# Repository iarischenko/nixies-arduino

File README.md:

# nixies-arduino
The repository contains sch, pcb and source code files for clock based on
IN12 nixie tubes.
The clock is based on custom stm32 board, MAX1771 boost converter, HV5812 high
voltage drivers, PEC16 encoder and FUSB302 usb pd phy.

## folder structure
freecad-project: case FreeCAD 3d models\
kicad-projects : pcb's KiCAD projects\
software       : libopencm3 based software for stm32 based MCU board

## IN12 v3
(master)

## IN12 v2
see v2 tag
### IN12 v2 (demo, clickable video)

## IN12 v1
see v1 tag
Prototype photo:

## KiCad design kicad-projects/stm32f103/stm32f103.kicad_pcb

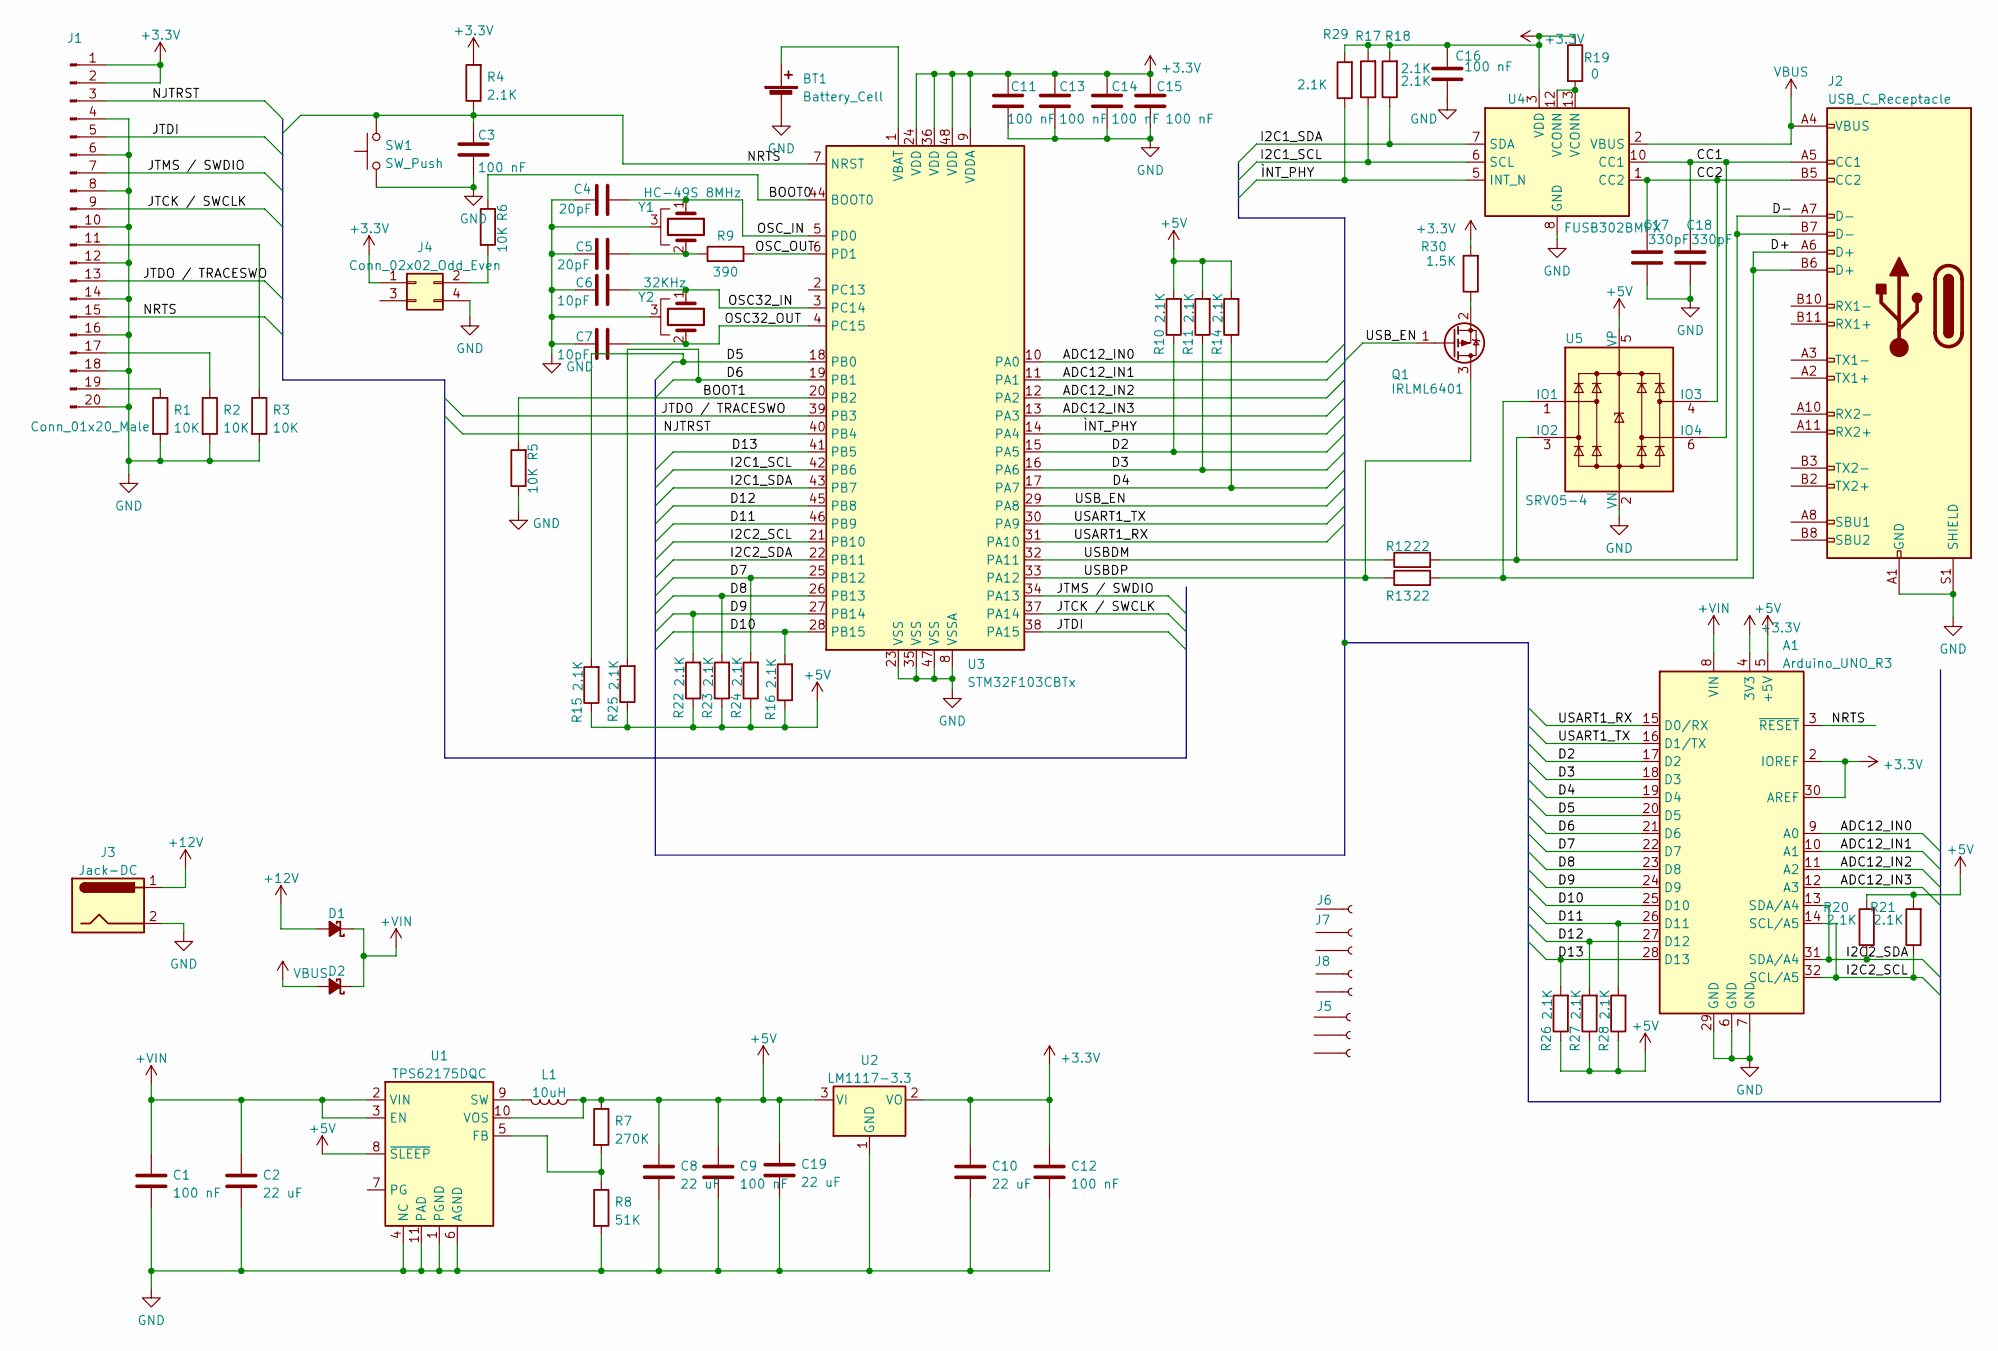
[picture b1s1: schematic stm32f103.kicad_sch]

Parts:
A1: Arduino_UNO_R3; Arduino_UNO_R3_WithMountingHoles_inverted
BT1: Battery_Cell; BatteryHolder_Keystone_1060_1x2032
C1, C3, C9, C11, C12, C13, C14, C15, C16: 100 nF; C_0805_2012Metric_Pad1.18x1.45mm_HandSolder
C2, C8, C10, C19: 22 uF; C_1206_3216Metric_Pad1.33x1.80mm_HandSolder
C4, C5: 20pF; C_0805_2012Metric_Pad1.18x1.45mm_HandSolder
C6, C7: 10pF; C_0805_2012Metric_Pad1.18x1.45mm_HandSolder
C17, C18: 330pF; C_0805_2012Metric_Pad1.18x1.45mm_HandSolder
D1, D2: D_Schottky_Small_Filled; D_SMA
J1: Conn_01x20_Male; PinHeader_2x10_P2.54mm_Vertical
J2: USB_C_Receptacle; USB_C_Receptacle_HRO_TYPE-C-31-M-12
J3: Jack-DC; BarrelJack_Horizontal
J4: Conn_02x02_Odd_Even; PinHeader_2x02_P2.54mm_Vertical
J5: Conn_01x10_Female; PinSocket_1x10_P2.54mm_Vertical
J6: Conn_01x06_Female; PinSocket_1x06_P2.54mm_Vertical
J7, J8: Conn_01x08_Female; PinSocket_1x08_P2.54mm_Vertical
L1: 10uH; L_Vishay_IHLP-4040
Q1: IRLML6401; SOT-23
R1, R2, R3, R5, R6: 10K; R_0805_2012Metric_Pad1.20x1.40mm_HandSolder
R4, R10, R11, R14, R15, R16, R17, R18, R20, R21, R22, R23, R24, R25, R26, R27, R28, R29: 2.1K; R_0805_2012Metric_Pad1.20x1.40mm_HandSolder
R7: 270K; R_0805_2012Metric_Pad1.20x1.40mm_HandSolder
R8: 51K; R_0805_2012Metric_Pad1.20x1.40mm_HandSolder
R9: 390; R_0805_2012Metric_Pad1.20x1.40mm_HandSolder
R12, R13: 22; R_0805_2012Metric_Pad1.20x1.40mm_HandSolder
R19: 0; R_0805_2012Metric_Pad1.20x1.40mm_HandSolder
R30: 1.5K; R_0805_2012Metric_Pad1.20x1.40mm_HandSolder
SW1: SW_Push; SW_Push_1P1T_NO_CK_KSC7xxJ
U1: TPS62175DQC; WSON-10-1EP_2x3mm_P0.5mm_EP0.84x2.4mm_ThermalVias
U2: LM1117-3.3; SOT-223-3_TabPin2
U3: STM32F103CBTx; LQFP-48_7x7mm_P0.5mm
U4: FUSB302BMPX; WQFN-14-1EP_2.5x2.5mm_P0.5mm_EP1.45x1.45mm
U5: SRV05-4; SOT-23-6
Y1: HC-49S 8MHz; Crystal_SMD_HC49-SD
Y2: 32KHz; Crystal_C38-LF_D3.0mm_L8.0mm_Horizontal_1EP_style2

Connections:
+3.3V: A1.2 (IOREF), A1.4 (3V3), A1.30 (AREF), C10.1, C11.1, C12.1, C13.1, C14.1, C15.1, C16.1, J1.1, J1.2, J4.1, R4.2, R17.2, R18.2, R19.1, R29.2, R30.2, U2.2 (VO), U3.9 (VDDA), U3.24 (VDD), U3.36 (VDD), U3.48 (VDD), U4.3 (VDD), U4.4 (VDD)
+5V: A1.5 (+5V), C8.1, C9.1, C19.1, L1.1, R7.1, R10.2, R11.2, R14.2, R15.1, R16.1, R20.2, R21.2, R22.1, R23.1, R24.1, R25.1, R26.1, R27.1, R28.1, U1.8 (~SLEEP), U1.10 (VOS), U2.3 (VI), U5.5 (VP)
+12V: D1.2 (A), J3.1
+VIN: A1.8 (VIN), C1.1, C2.1, D1.1 (K), D2.1 (K), U1.2 (VIN), U1.3 (EN)
/ADC12_IN0: A1.9 (A0), U3.10 (PA0)
/ADC12_IN1: A1.10 (A1), U3.11 (PA1)
/ADC12_IN2: A1.11 (A2), U3.12 (PA2)
/ADC12_IN3: A1.12 (A3), U3.13 (PA3)
/BOOT0: R6.1, U3.44 (BOOT0)
/BOOT1: R5.2, U3.20 (PB2)
/CC1: C18.2, J2.A5 (CC1), U4.10 (CC1), U4.11 (CC1), U5.6 (IO4)
/CC2: C17.2, J2.B5 (CC2), U4.1 (CC2), U4.14 (CC2), U5.4 (IO3)
/D2: A1.17 (D2), R10.1, U3.15 (PA5)
/D3: A1.18 (D3), R11.1, U3.16 (PA6)
/D4: A1.19 (D4), R14.1, U3.17 (PA7)
/D5: A1.20 (D5), R15.2, U3.18 (PB0)
/D6: A1.21 (D6), R25.2, U3.19 (PB1)
/D7: A1.22 (D7), R24.2, U3.25 (PB12)
/D8: A1.23 (D8), R23.2, U3.26 (PB13)
/D9: A1.24 (D9), R22.2, U3.27 (PB14)
/D10: A1.25 (D10), R16.2, U3.28 (PB15)
/D11: A1.26 (D11), R28.2, U3.46 (PB9)
/D12: A1.27 (D12), R27.2, U3.45 (PB8)
/D13: A1.28 (D13), R26.2, U3.41 (PB5)
/D+: J2.A6 (D+), J2.B6 (D+), R13.2, U5.1 (IO1)
/D-: J2.A7 (D-), J2.B7 (D-), R12.2, U5.3 (IO2)
/I2C1_SCL: R17.1, U3.42 (PB6), U4.6 (SCL)
/I2C1_SDA: R18.1, U3.43 (PB7), U4.7 (SDA)
/I2C2_SCL: A1.14 (SCL/A5), A1.32 (SCL/A5), R21.1, U3.21 (PB10)
/I2C2_SDA: A1.13 (SDA/A4), A1.31 (SDA/A4), R20.1, U3.22 (PB11)
/JTCK / SWCLK: J1.9, U3.37 (PA14)
/JTDI: J1.5, U3.38 (PA15)
/JTDO / TRACESWO: J1.13, U3.39 (PB3)
/JTMS / SWDIO: J1.7, U3.34 (PA13)
/NJTRST: J1.3, U3.40 (PB4)
/NRTS: A1.3 (~RESET), C3.1, J1.15, R4.1, SW1.2, U3.7 (NRST)
/OSC32_IN: C6.2, U3.3 (PC14), Y2.1
/OSC32_OUT: C7.2, U3.4 (PC15), Y2.2
/OSC_IN: C4.2, U3.5 (PD0), Y1.1
/OSC_OUT: R9.2, U3.6 (PD1)
/USART1_RX: A1.15 (D0/RX), U3.31 (PA10)
/USART1_TX: A1.16 (D1/TX), U3.30 (PA9)
/USBDM: R12.1, U3.32 (PA11)
/USBDP: Q1.3 (D), R13.1, U3.33 (PA12)
/USB_EN: Q1.1 (G), U3.29 (PA8)
/ÌNT_PHY: R29.1, U3.14 (PA4), U4.5 (INT_N)
GND: A1.6 (GND), A1.7 (GND), A1.29 (GND), BT1.2 (-), C1.2, C2.2, C3.2, C4.1, C5.1, C6.1, C7.1, C8.2, C9.2, C10.2, C11.2, C12.2, C13.2, C14.2, C15.2, C16.2, C17.1, C18.1, C19.2, J1.4, J1.6, J1.8, J1.10, J1.12, J1.14, J1.16, J1.18, J1.20, J2.A1 (GND), J2.A12 (GND), J2.B1 (GND), J2.B12 (GND), J2.S1 (SHIELD), J3.2, J4.4, R1.2, R2.2, R3.2, R5.1, R8.2, SW1.1, U1.1 (PGND), U1.4 (NC), U1.6 (AGND), U1.11 (PAD), U2.1 (GND), U3.8 (VSSA), U3.23 (VSS), U3.35 (VSS), U3.47 (VSS), U4.8 (GND), U4.9 (GND), U4.15 (GND), U5.2 (VN), Y1.3, Y2.3
unnamed: BT1.1 (+), U3.1 (VBAT)
unnamed: C5.2, R9.1, Y1.2
unnamed: J1.11, R3.1
unnamed: J1.17, R2.1
unnamed: J1.19, R1.1
unnamed: J4.2, R6.2
unnamed: L1.2, U1.9 (SW)
unnamed: Q1.2 (S), R30.1
unnamed: R7.2, R8.1, U1.5 (FB)
unnamed: R19.2, U4.12 (VCONN), U4.13 (VCONN)
VBUS: D2.2 (A), J2.A4 (VBUS), J2.A9 (VBUS), J2.B4 (VBUS), J2.B9 (VBUS), U4.2 (VBUS)

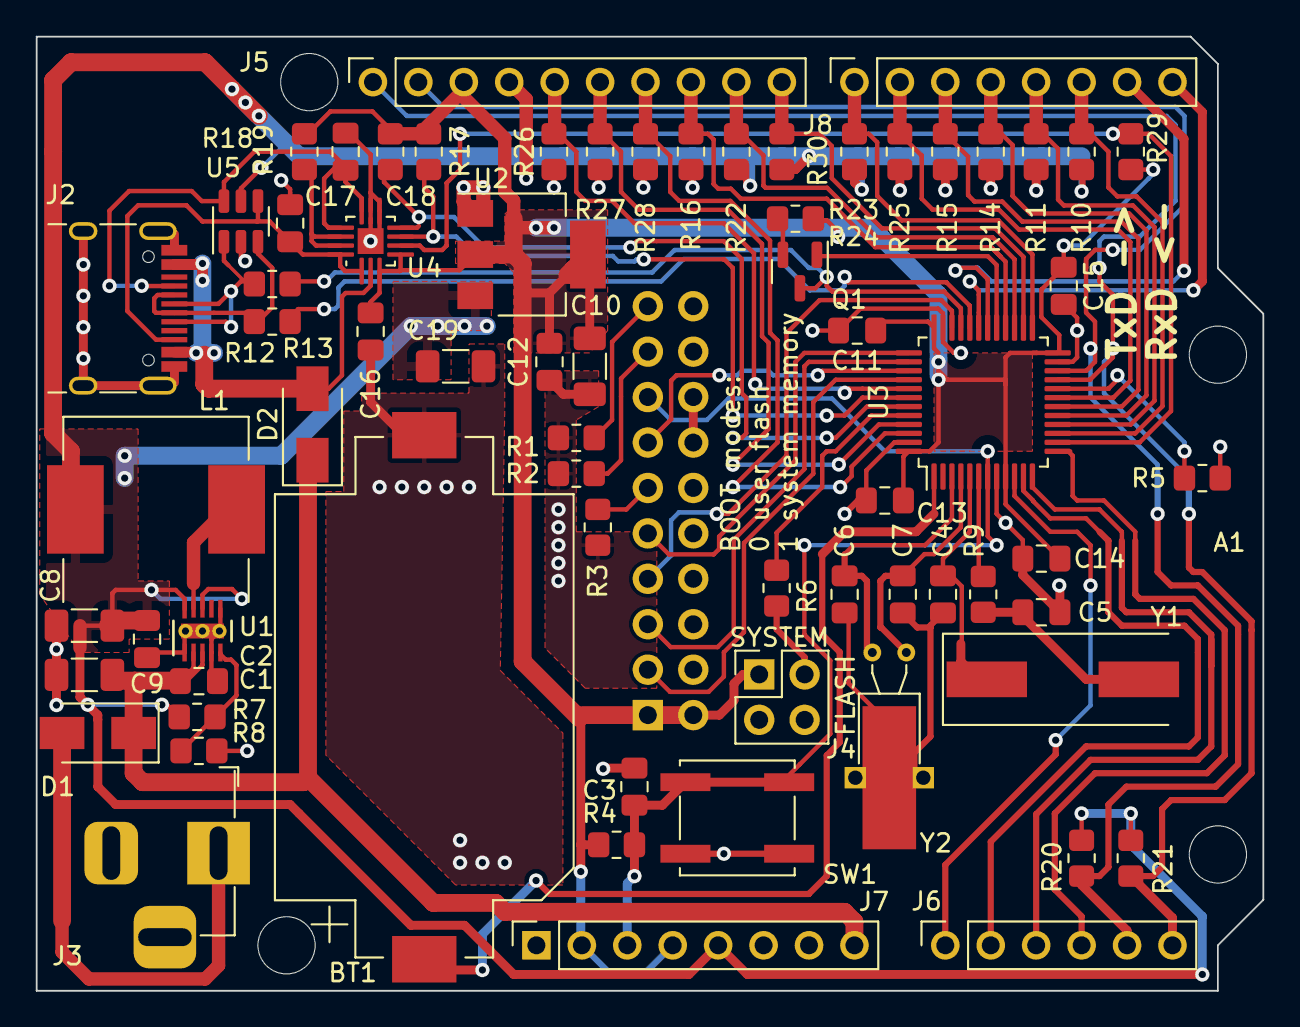
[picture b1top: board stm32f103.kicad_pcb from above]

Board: 2 copper layers, 68.6 x 53.3 mm, 71 parts (1 on the bottom side), 58 nets.

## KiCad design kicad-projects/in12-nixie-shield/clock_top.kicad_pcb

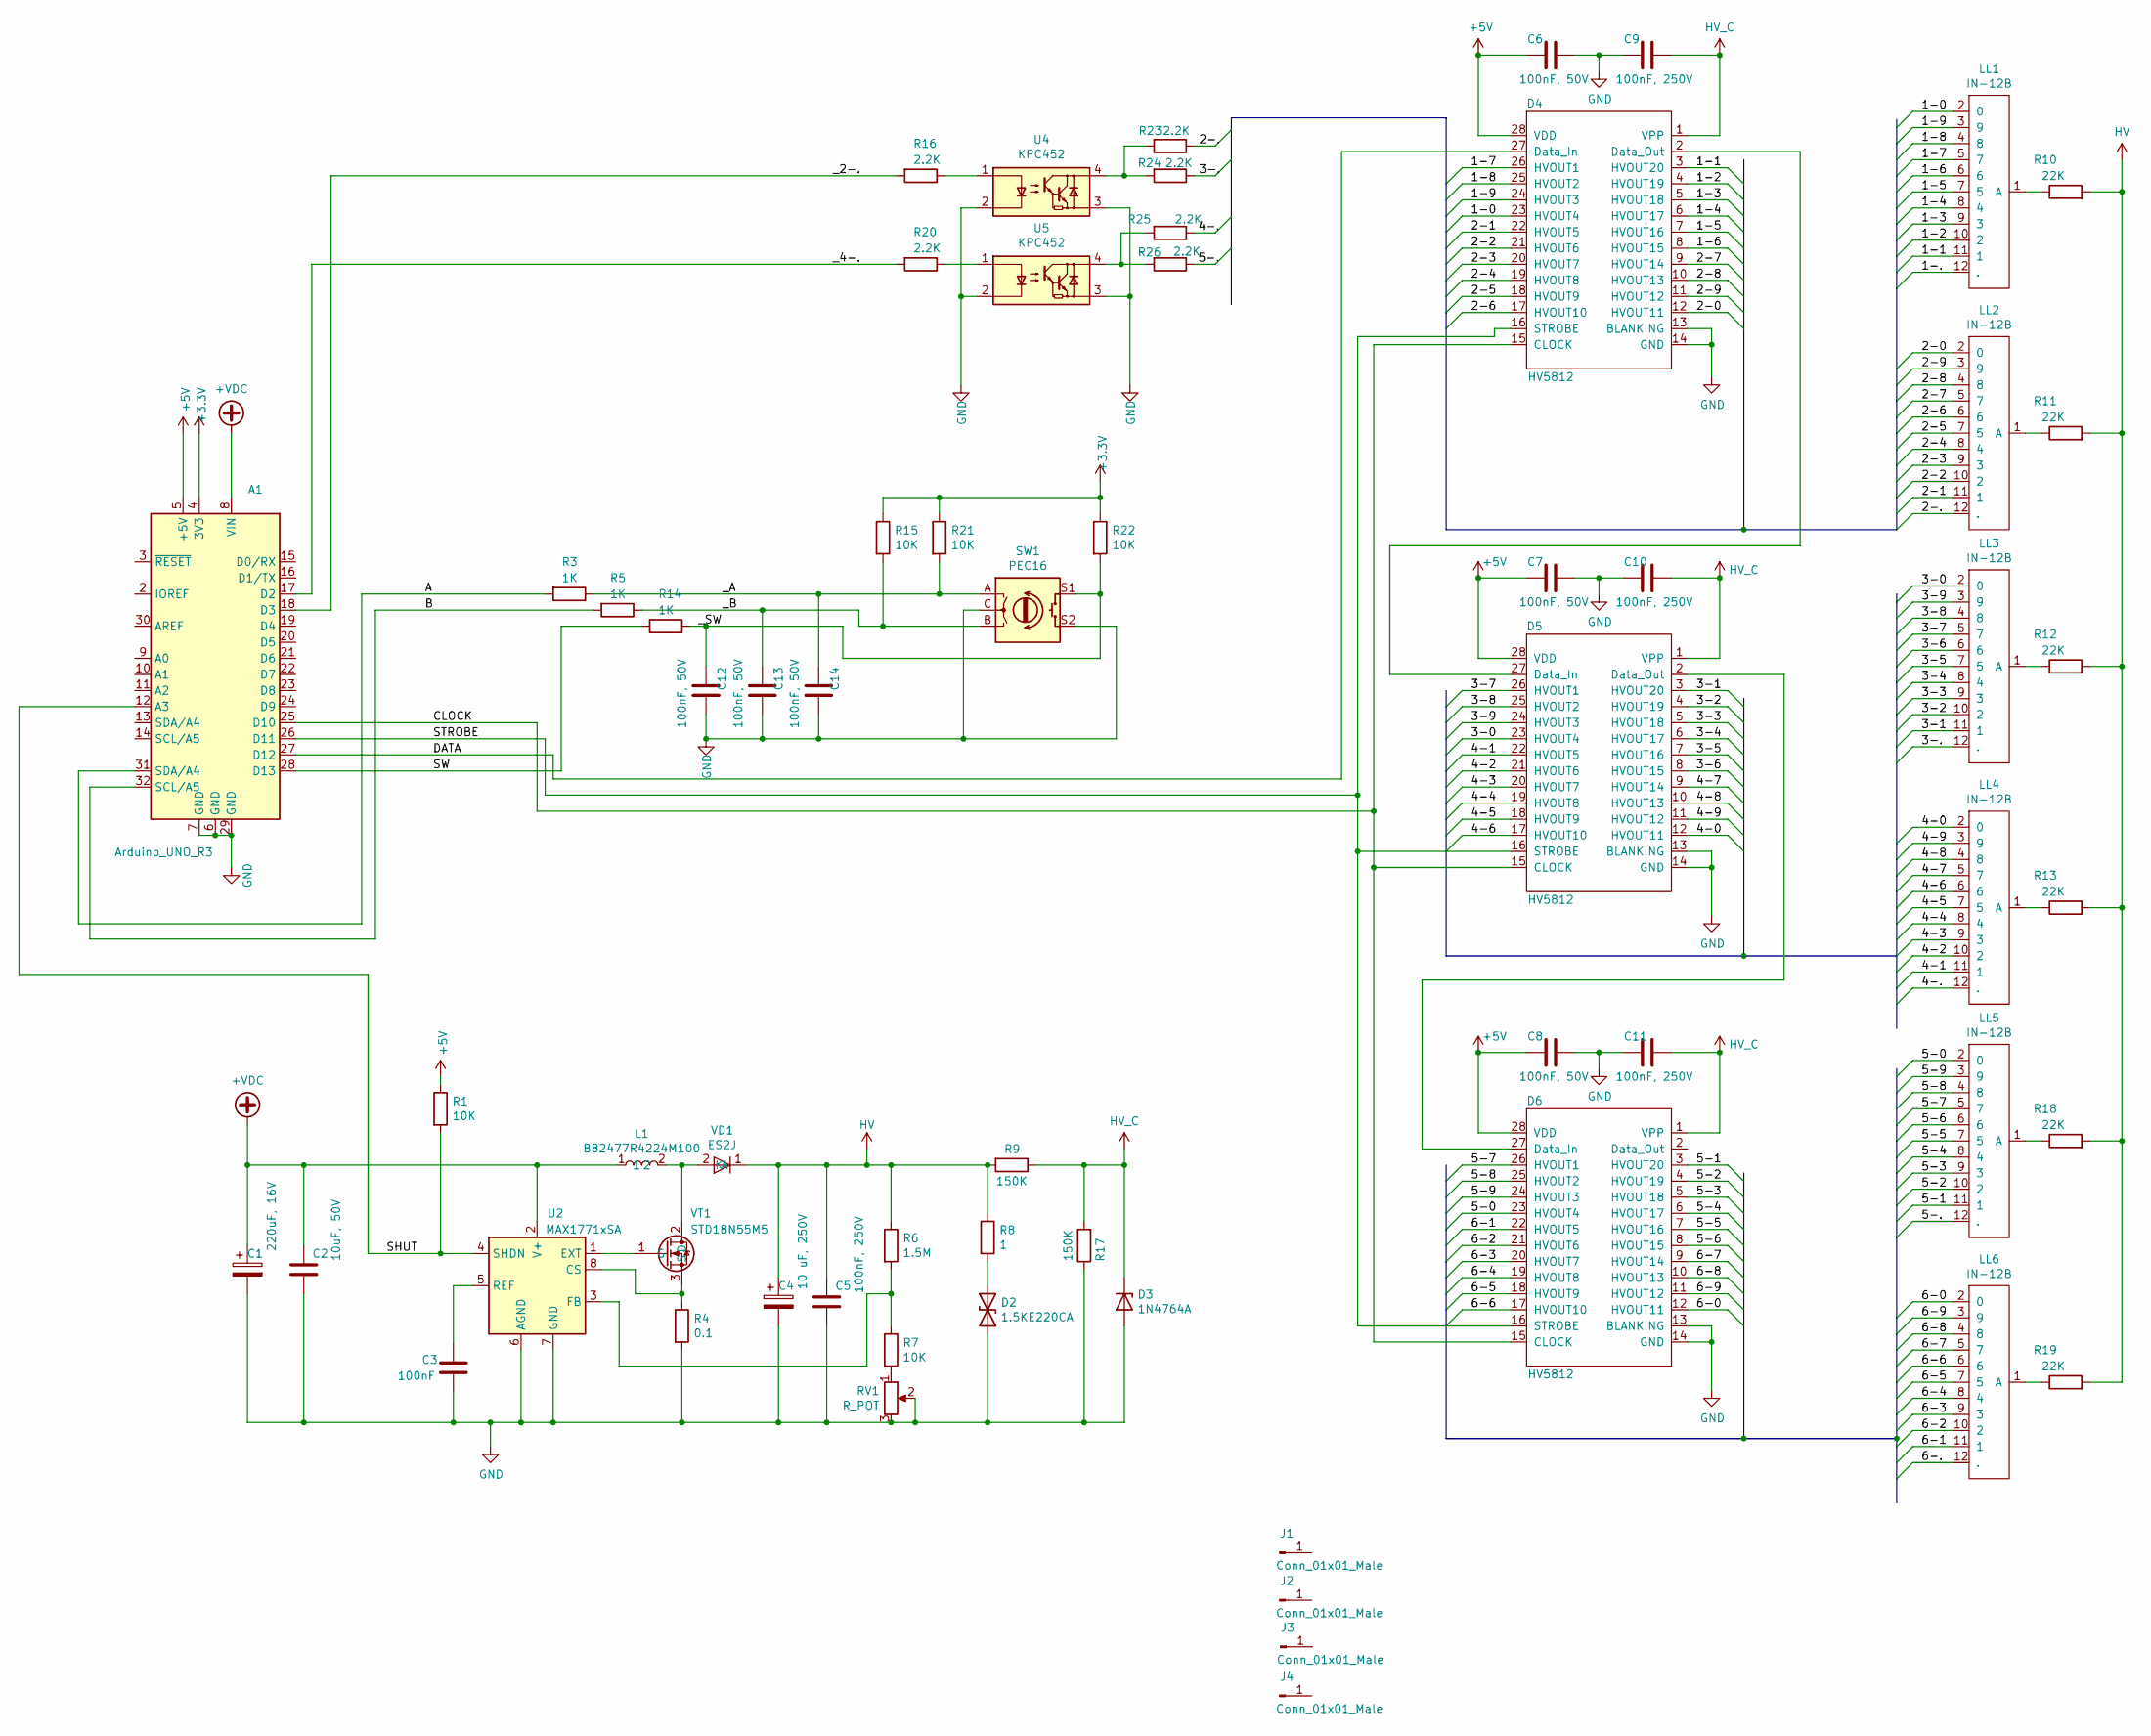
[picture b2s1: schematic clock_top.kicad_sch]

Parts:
A1: Arduino_UNO_R3
C1: 220uF, 16V; CP_Radial_D6.3mm_P2.50mm
C2: 10uF, 50V; C_1210_3225Metric_Pad1.33x2.70mm_HandSolder
C3: 100nF; C_0805_2012Metric_Pad1.15x1.40mm_HandSolder
C4: 10 uF, 250V; C_Axial_L22.0mm_D10.5mm_P27.50mm_Horizontal
C5, C9, C10: 100nF, 250V; C_1206_3216Metric_Pad1.42x1.75mm_HandSolder
C6, C7, C8: 100nF, 50V; C_0805_2012Metric_Pad1.15x1.40mm_HandSolder
C11: 100nF, 250V; C_1206_3216Metric_Pad1.33x1.80mm_HandSolder
C12, C13, C14: 100nF, 50V; C_0805_2012Metric_Pad1.18x1.45mm_HandSolder
D2: 1.5KE220CA; D_DO-201AE_P15.24mm_Horizontal
D3: 1N4764A; D_DO-41_SOD81_P10.16mm_Horizontal
D4, D5, D6: HV5812; SOIC-28W_7.5x17.9mm_P1.27mm
J1, J4: Conn_01x01_Male; PinHeader_1x08_P2.54mm_Vertical
J2: Conn_01x01_Male; PinHeader_1x06_P2.54mm_Vertical
J3: Conn_01x01_Male; PinHeader_1x10_P2.54mm_Vertical
L1: B82477R4224M100; L_12x12mm_H8mm
LL1, LL2, LL3, LL4, LL5, LL6: IN-12B; IN12-HI_IE
R1, R15, R21, R22: 10K; R_0805_2012Metric_Pad1.20x1.40mm_HandSolder
R3, R5, R14: 1K; R_0805_2012Metric_Pad1.20x1.40mm_HandSolder
R4: 0.1; R_2512_6332Metric_Pad1.40x3.35mm_HandSolder
R6: 1.5M; R_0805_2012Metric_Pad1.20x1.40mm_HandSolder
R7: 10K; R_0805_2012Metric
R8: 1; R_1206_3216Metric_Pad1.30x1.75mm_HandSolder
R9, R17: 150K; R_0805_2012Metric_Pad1.20x1.40mm_HandSolder
R10, R11, R12, R13, R18, R19: 22K; R_0805_2012Metric_Pad1.15x1.40mm_HandSolder
R16, R20, R23, R24, R25, R26: 2.2K; R_0805_2012Metric_Pad1.20x1.40mm_HandSolder
RV1: R_POT; 3362P
SW1: PEC16
U2: MAX1771xSA; SO-8_3.9x4.9mm_P1.27mm
U4, U5: KPC452; SO-4_4.4x3.6mm_P2.54mm
VD1: ES2J; D_SMB_Handsoldering
VT1: STD18N55M5; TO-252-2

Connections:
+3V3: A1.4 (3V3), R15.1, R21.1, R22.1
+5V: A1.5 (+5V), C6.2, C7.2, C8.2, D4.28 (VDD), D5.28 (VDD), D6.28 (VDD), R1.1
+VDC: A1.8 (VIN), C1.1, C2.1, L1.1, U2.2 (V+)
/1-0: D4.23 (HVOUT4), LL1.2 (0)
/1-1: D4.3 (HVOUT20), LL1.11 (1)
/1-2: D4.4 (HVOUT19), LL1.10 (2)
/1-3: D4.5 (HVOUT18), LL1.9 (3)
/1-4: D4.6 (HVOUT17), LL1.8 (4)
/1-5: D4.7 (HVOUT16), LL1.7 (5)
/1-6: D4.8 (HVOUT15), LL1.6
/1-7: D4.26 (HVOUT1), LL1.5 (7)
/1-8: D4.25 (HVOUT2), LL1.4 (8)
/1-9: D4.24 (HVOUT3), LL1.3 (9)
/1-.: LL1.12 (.)
/2-0: D4.12 (HVOUT11), LL2.2 (0)
/2-1: D4.22 (HVOUT5), LL2.11 (1)
/2-2: D4.21 (HVOUT6), LL2.10 (2)
/2-3: D4.20 (HVOUT7), LL2.9 (3)
/2-4: D4.19 (HVOUT8), LL2.8 (4)
/2-5: D4.18 (HVOUT9), LL2.7 (5)
/2-6: D4.17 (HVOUT10), LL2.6
/2-7: D4.9 (HVOUT14), LL2.5 (7)
/2-8: D4.10 (HVOUT13), LL2.4 (8)
/2-9: D4.11 (HVOUT12), LL2.3 (9)
/2-.: LL2.12 (.), R23.1
/3-0: D5.23 (HVOUT4), LL3.2 (0)
/3-1: D5.3 (HVOUT20), LL3.11 (1)
/3-2: D5.4 (HVOUT19), LL3.10 (2)
/3-3: D5.5 (HVOUT18), LL3.9 (3)
/3-4: D5.6 (HVOUT17), LL3.8 (4)
/3-5: D5.7 (HVOUT16), LL3.7 (5)
/3-6: D5.8 (HVOUT15), LL3.6
/3-7: D5.26 (HVOUT1), LL3.5 (7)
/3-8: D5.25 (HVOUT2), LL3.4 (8)
/3-9: D5.24 (HVOUT3), LL3.3 (9)
/3-.: LL3.12 (.), R24.1
/4-0: D5.12 (HVOUT11), LL4.2 (0)
/4-1: D5.22 (HVOUT5), LL4.11 (1)
/4-2: D5.21 (HVOUT6), LL4.10 (2)
/4-3: D5.20 (HVOUT7), LL4.9 (3)
/4-4: D5.19 (HVOUT8), LL4.8 (4)
/4-5: D5.18 (HVOUT9), LL4.7 (5)
/4-6: D5.17 (HVOUT10), LL4.6
/4-7: D5.9 (HVOUT14), LL4.5 (7)
/4-8: D5.10 (HVOUT13), LL4.4 (8)
/4-9: D5.11 (HVOUT12), LL4.3 (9)
/4-.: LL4.12 (.), R25.1
/5-0: D6.23 (HVOUT4), LL5.2 (0)
/5-1: D6.3 (HVOUT20), LL5.11 (1)
/5-2: D6.4 (HVOUT19), LL5.10 (2)
/5-3: D6.5 (HVOUT18), LL5.9 (3)
/5-4: D6.6 (HVOUT17), LL5.8 (4)
/5-5: D6.7 (HVOUT16), LL5.7 (5)
/5-6: D6.8 (HVOUT15), LL5.6
/5-7: D6.26 (HVOUT1), LL5.5 (7)
/5-8: D6.25 (HVOUT2), LL5.4 (8)
/5-9: D6.24 (HVOUT3), LL5.3 (9)
/5-.: LL5.12 (.), R26.1
/6-0: D6.12 (HVOUT11), LL6.2 (0)
/6-1: D6.22 (HVOUT5), LL6.11 (1)
/6-2: D6.21 (HVOUT6), LL6.10 (2)
/6-3: D6.20 (HVOUT7), LL6.9 (3)
/6-4: D6.19 (HVOUT8), LL6.8 (4)
/6-5: D6.18 (HVOUT9), LL6.7 (5)
/6-6: D6.17 (HVOUT10), LL6.6
/6-7: D6.9 (HVOUT14), LL6.5 (7)
/6-8: D6.10 (HVOUT13), LL6.4 (8)
/6-9: D6.11 (HVOUT12), LL6.3 (9)
/6-.: LL6.12 (.)
/A: A1.31 (SDA/A4), R3.2
/B: A1.32 (SCL/A5), R5.2
/CLOCK: A1.25 (D10), D4.15 (CLOCK), D5.15 (CLOCK), D6.15 (CLOCK)
/DATA: A1.27 (D12), D4.27 (Data_In)
/SHUT: A1.12 (A3), R1.2, U2.4 (SHDN)
/STROBE: A1.26 (D11), D4.16 (STROBE), D5.16 (STROBE), D6.16 (STROBE)
/SW: A1.28 (D13), R14.2
/_2-.: A1.18 (D3), R16.2
/_4-.: A1.17 (D2), R20.2
/_A: C14.2, R3.1, R21.2, SW1.A
/_B: C13.2, R5.1, R15.2, SW1.B
/_SW: C12.2, R14.1, R22.2, SW1.S1
GND: A1.6 (GND), A1.7 (GND), A1.29 (GND), C1.2, C2.2, C3.2, C4.2, C5.2, C6.1, C7.1, C8.1, C9.2, C10.2, C11.2, C12.1, C13.1, C14.1, D2.2 (A2), D3.2 (A), D4.13 (BLANKING), D4.14 (GND), D5.13 (BLANKING), D5.14 (GND), D6.13 (BLANKING), D6.14 (GND), R4.2, R17.1, RV1.2, RV1.3, SW1.C, SW1.S2, U2.6 (AGND), U2.7 (GND), U4.2, U4.3, U5.2, U5.3
HV: C4.1, C5.1, R6.1, R8.1, R9.2, R10.2, R11.2, R12.2, R13.2, R18.2, R19.2, VD1.1 (K)
HV_C: C9.1, C10.1, C11.1, D3.1 (K), D4.1 (VPP), D5.1 (VPP), D6.1 (VPP), R9.1, R17.2
unnamed: C3.1, U2.5 (REF)
unnamed: D2.1 (A1), R8.2
unnamed: D4.2 (Data_Out), D5.27 (Data_In)
unnamed: D5.2 (Data_Out), D6.27 (Data_In)
unnamed: L1.2, VD1.2 (A), VT1.2 (D)
unnamed: LL1.1 (A), R10.1
unnamed: LL2.1 (A), R11.1
unnamed: LL3.1 (A), R12.1
unnamed: LL4.1 (A), R13.1
unnamed: LL5.1 (A), R18.1
unnamed: LL6.1 (A), R19.1
unnamed: R4.1, U2.8 (CS), VT1.3 (S)
unnamed: R6.2, R7.1, U2.3 (FB)
unnamed: R7.2, RV1.1
unnamed: R16.1, U4.1
unnamed: R20.1, U5.1
unnamed: R23.2, R24.2, U4.4
unnamed: R25.2, R26.2, U5.4
unnamed: U2.1 (EXT), VT1.1 (G)

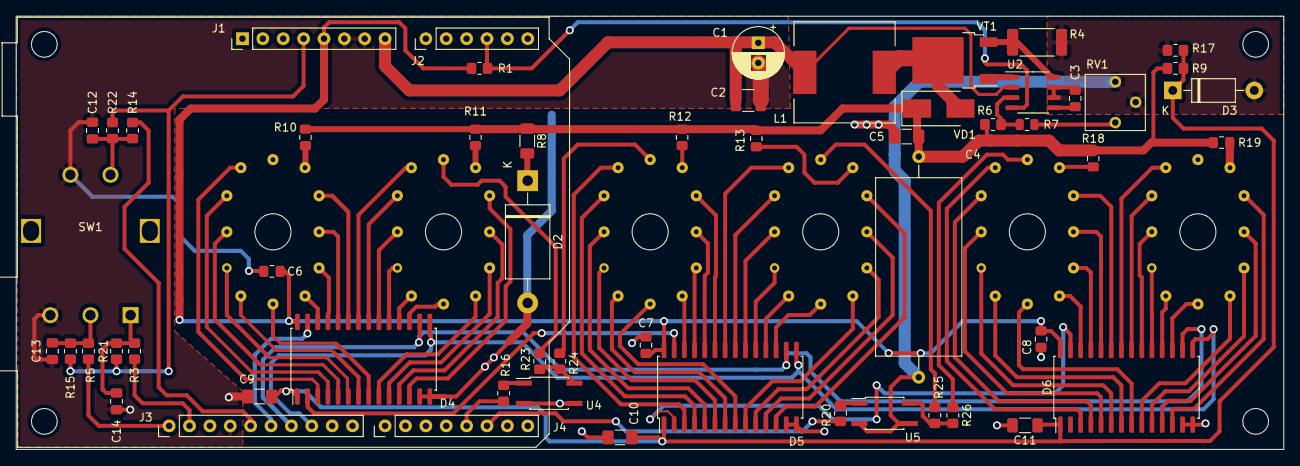
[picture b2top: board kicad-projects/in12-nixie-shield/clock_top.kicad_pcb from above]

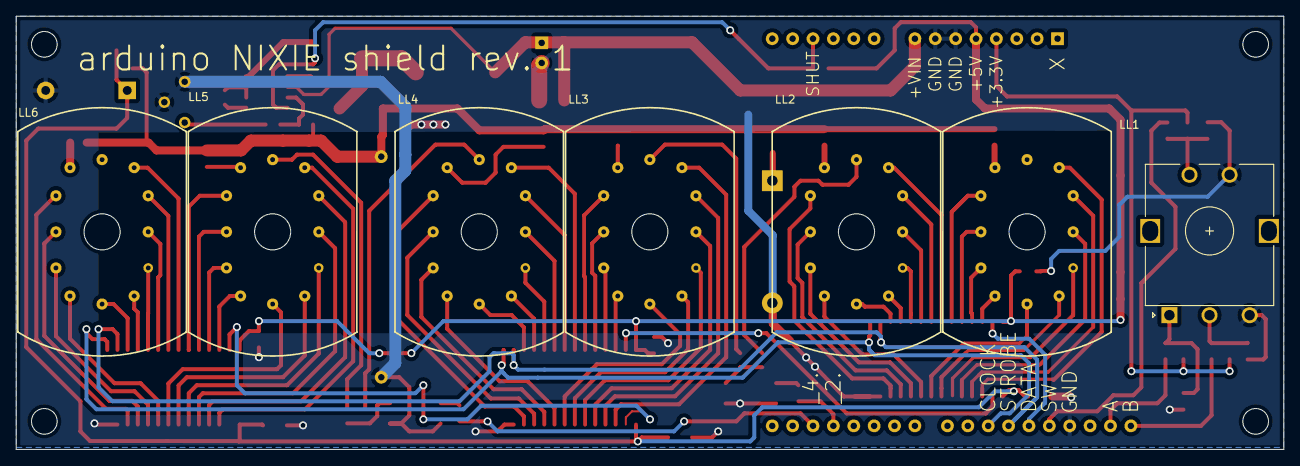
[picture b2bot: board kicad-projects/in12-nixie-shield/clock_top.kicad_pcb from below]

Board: 2 copper layers, 158.0 x 54.0 mm, 63 parts (6 on the bottom side), 101 nets.

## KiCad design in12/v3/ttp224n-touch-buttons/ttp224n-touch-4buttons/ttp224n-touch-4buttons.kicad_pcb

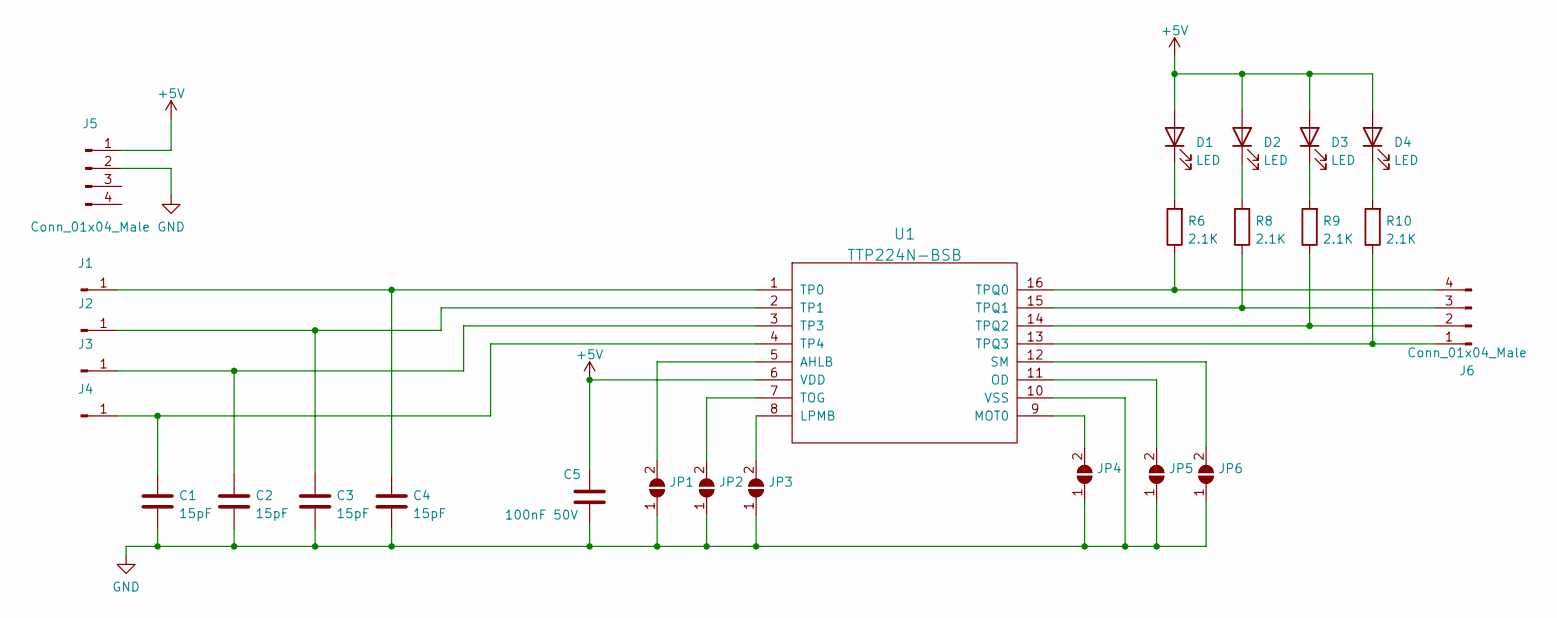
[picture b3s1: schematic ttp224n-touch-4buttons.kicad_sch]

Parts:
C1, C2, C3, C4: 15pF; C_0805_2012Metric_Pad1.18x1.45mm_HandSolder
C5: 100nF 50V; C_0805_2012Metric_Pad1.18x1.45mm_HandSolder
D1, D2, D3, D4: LED; D_0805_2012Metric_Pad1.15x1.40mm_HandSolder
J1, J2, J3, J4: Conn_01x01_Male; cap_button
J5, J6: Conn_01x04_Male; PinSocket_1x04_P2.54mm_Vertical_SMD_Pin1Left
JP1, JP2, JP3, JP4, JP5, JP6: SolderJumper_2_Open; SolderJumper-2_P1.3mm_Open_RoundedPad1.0x1.5mm
R6, R8, R9, R10: 2.1K; R_0805_2012Metric_Pad1.20x1.40mm_HandSolder
U1: TTP224N-BSB; SSOP-16_3.9x4.9mm_P0.635mm

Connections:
+5V: C5.1, D1.2 (A), D2.2 (A), D3.2 (A), D4.2 (A), J5.1, U1.6 (VDD)
GND: C1.2, C2.2, C3.2, C4.2, C5.2, J5.2, JP1.1 (A), JP2.1 (A), JP3.1 (A), JP4.1 (A), JP5.1 (A), JP6.1 (A), U1.10 (VSS)
unnamed: C1.1, J4.1, U1.4 (TP4)
unnamed: C2.1, J3.1, U1.3 (TP3)
unnamed: C3.1, J2.1, U1.2 (TP1)
unnamed: C4.1, J1.1, U1.1 (TP0)
unnamed: D1.1 (K), R6.2
unnamed: D2.1 (K), R8.2
unnamed: D3.1 (K), R9.2
unnamed: D4.1 (K), R10.2
unnamed: J6.1, R10.1, U1.13 (TPQ3)
unnamed: J6.2, R9.1, U1.14 (TPQ2)
unnamed: J6.3, R8.1, U1.15 (TPQ1)
unnamed: J6.4, R6.1, U1.16 (TPQ0)
unnamed: JP1.2 (B), U1.5 (AHLB)
unnamed: JP2.2 (B), U1.7 (TOG)
unnamed: JP3.2 (B), U1.8 (LPMB)
unnamed: JP4.2 (B), U1.9 (MOT0)
unnamed: JP5.2 (B), U1.11 (OD)
unnamed: JP6.2 (B), U1.12 (SM)

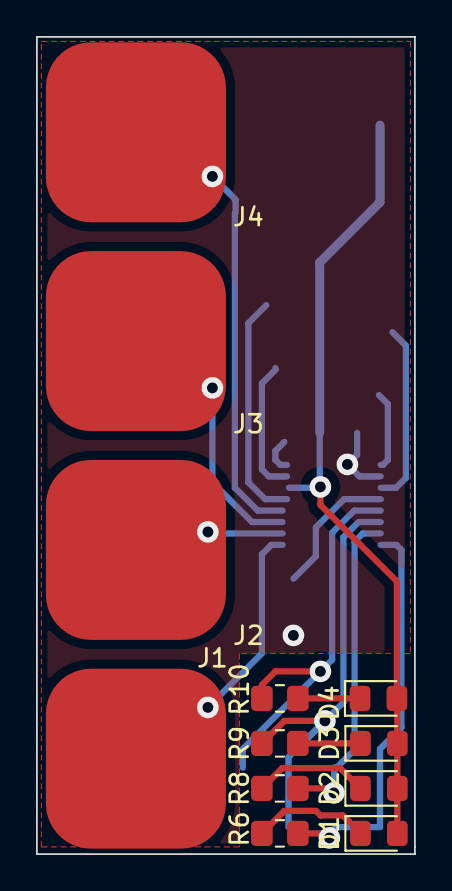
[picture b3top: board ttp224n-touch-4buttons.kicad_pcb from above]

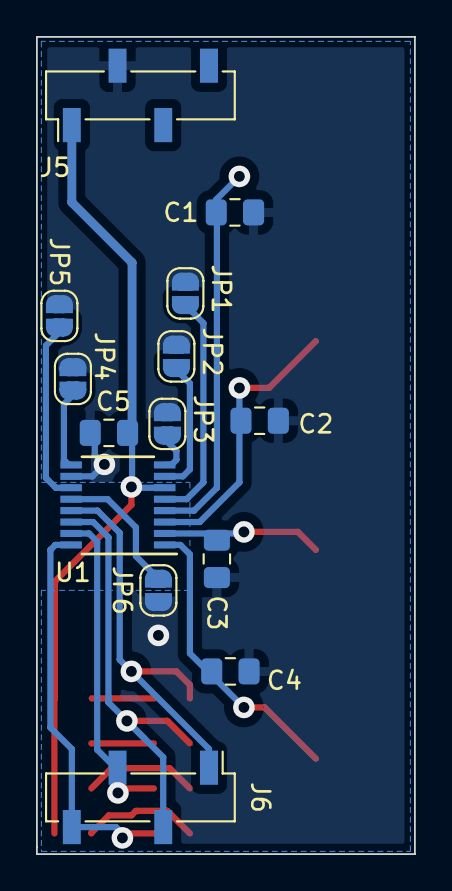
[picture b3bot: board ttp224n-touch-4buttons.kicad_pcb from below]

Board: 2 copper layers, 21.0 x 45.4 mm, 26 parts (14 on the bottom side), 20 nets.
